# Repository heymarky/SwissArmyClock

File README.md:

SwissArmyClock
==============

Arduino Project

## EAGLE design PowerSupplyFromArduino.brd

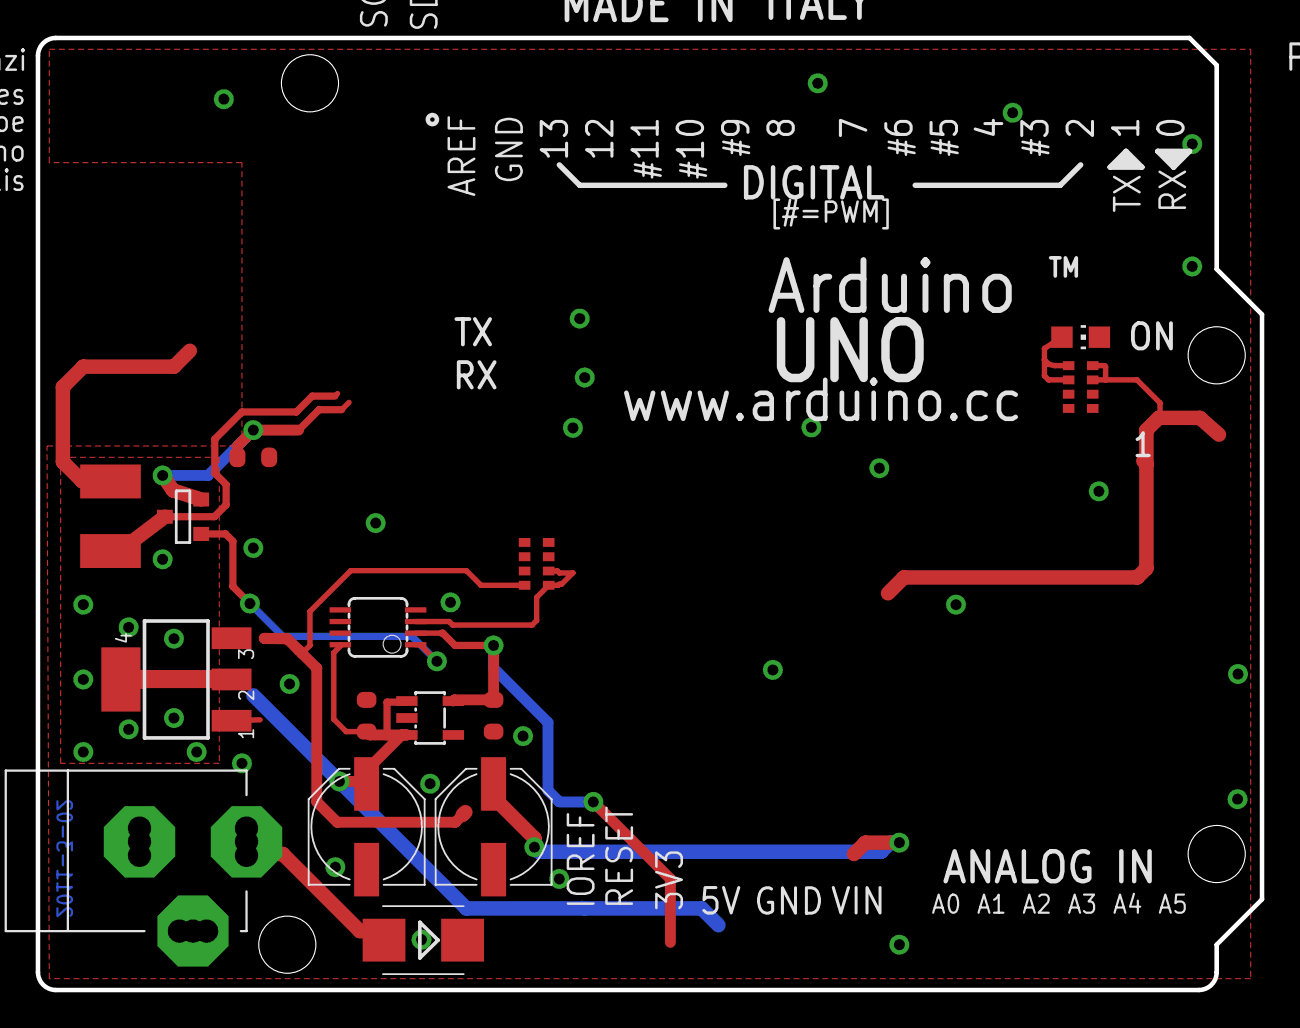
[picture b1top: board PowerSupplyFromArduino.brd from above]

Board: 2 copper layers, 68.6 x 53.3 mm, 15 parts (0 on the bottom side), 9 nets.

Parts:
C1, C2: 100n; C0603-ROUND
C3: 1u; C0603-ROUND
D1: M7; SMB
F1: MF-MSMF050-2 500mA; L1812
ON: GREEN; CHIP-LED0805
PC1, PC2: 47u; PANASONIC_D
RN1: 10K; CAY16
RN4: 1K; CAY16
T1: FDN340P; SOT-23
U1: NCP1117ST50T3G; SOT223
U2: LP2985-33DBVR; SOT23-DBV
U5: LMV358IDGKR; MSOP08
X1: POWERSUPPLY_DC21MMX; POWERSUPPLY_DC-21MM

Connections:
+3V3: C3.2, U2.5, U5.2
+5V: C1.2, RN4.3, RN4.4, T1.2, U2.1, U2.3, U5.8
CMP: RN1.1, RN1.2, U5.3
GATE_CMD: T1.3, U5.1
GND: C1.1, C2.1, C3.1, ON.C, PC1.-, PC2.-, RN1.7, U1.1, U2.2, U5.4, X1.1, X1.3
JACKVCC: C2.2, F1.2, PC2.+, T1.1, U1.2, U1.4
unnamed: D1.C, PC1.+, U1.3
unnamed: ON.A, RN4.5, RN4.6
PWRIN: D1.A, X1.2

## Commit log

2012-08-29 Move project to GIT
